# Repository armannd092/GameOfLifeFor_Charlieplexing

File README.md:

# GameOfLifeFor_Charlieplexing
It is a fun project for practicing electronic and algorithm.

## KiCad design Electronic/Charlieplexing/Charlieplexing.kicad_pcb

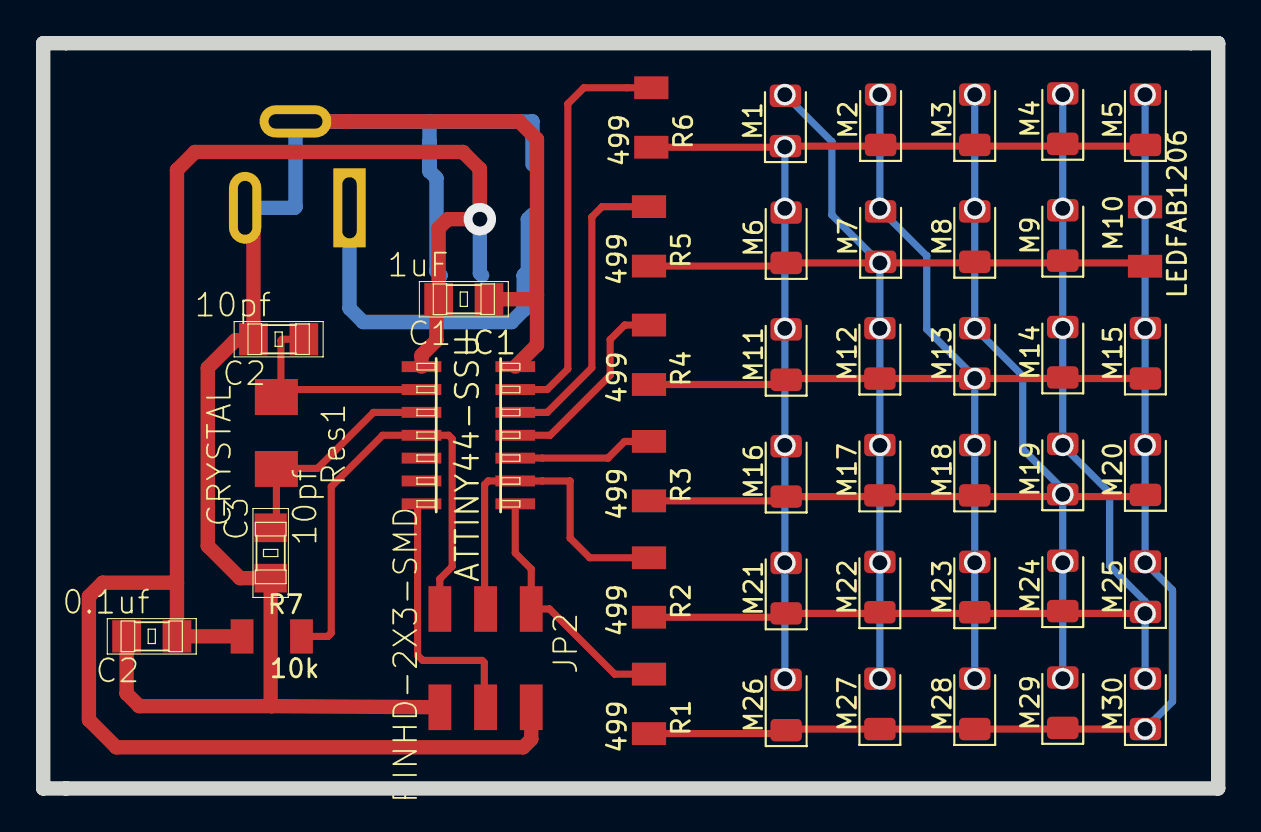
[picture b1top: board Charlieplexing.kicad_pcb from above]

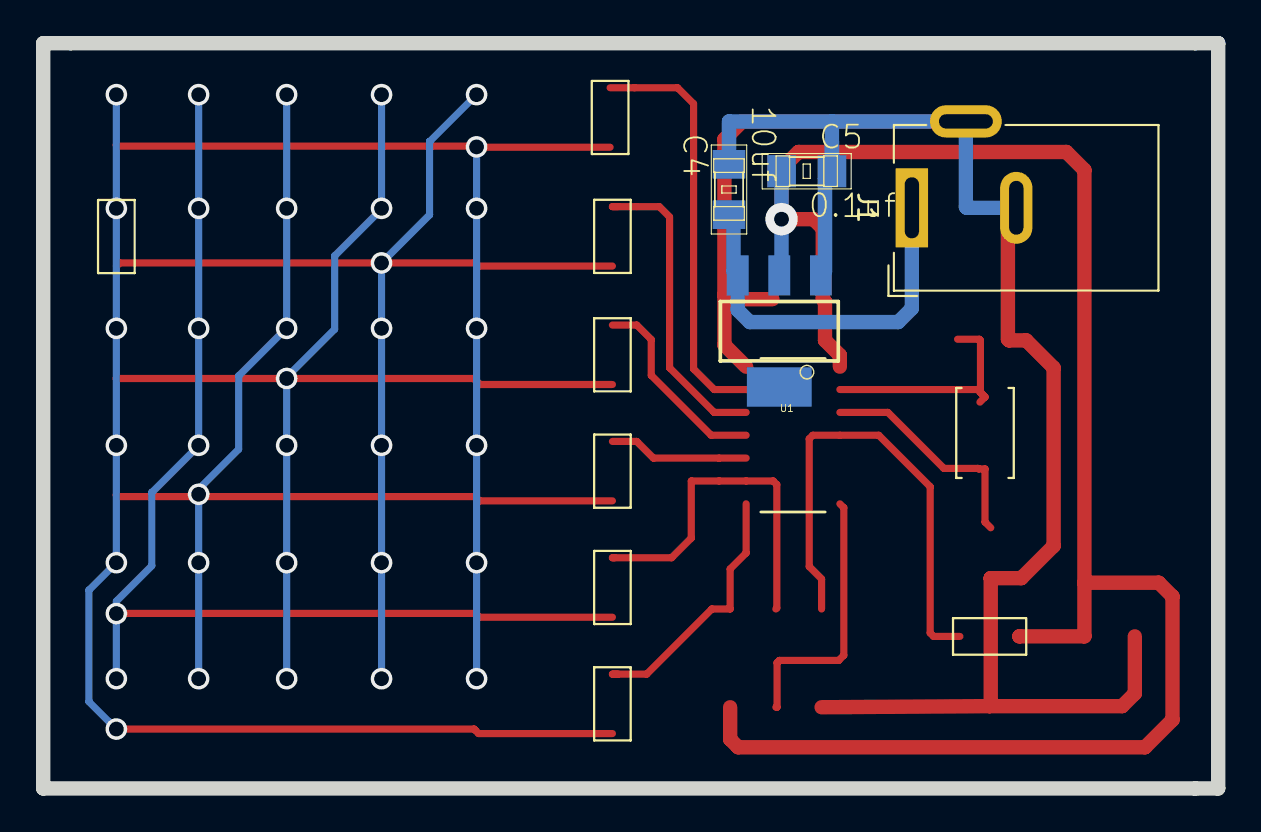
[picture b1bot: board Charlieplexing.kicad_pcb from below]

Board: 2 copper layers, 65.3 x 41.4 mm, 48 parts (4 on the bottom side), 19 nets.

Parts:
C1: 1uF; fab-C1206
C2, C5: 0.1uf; fab-C1206
C2#2, C3: 10pf; fab-C1206
C4: 10uf; fab-C1206
IC1: ATTINY44-SSU; fab-SOIC14
J1: Connector_Barrel_Jack_Switch; BarrelJack_Wuerth_6941xx301002
JP2: PINHD-2X3-SMD; fab-2X03SMD
M1, M2, M3, M4, M5, M6, M7, M8, M9, M11, M12, M13, M14, M15, M16, M17, M18, M19, M20, M21, M22, M23, M24, M25, M26, M27, M28, M29, M30: LEDFAB1206; LED_1206_3216Metric
M10: LEDFAB1206; fab-LED1206FAB
R1, R2, R3, R4, R5, R6: 499; fab-R1206FAB
R7: 10k; fab-R1206FAB
Res1: CRYSTAL; fab-2-SMD-5X3MM
U1: VOLTAGE-REGULATOR-SOT223; fab-SOT223

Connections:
5V: C1.2, C2.1, C5.1, IC1.1, JP2.2, R7.1, U1.2
GND: C1.1, C2.2, C2#2.2, C3.1, C4.2, C5.2, IC1.14, J1.2, J1.3, JP2.6, U1.1
MISO: IC1.8, JP2.1, R1.1
MOSI: IC1.7, JP2.4
unnamed: IC1.10, R3.1
unnamed: IC1.11, R4.1
unnamed: IC1.12, R5.1
unnamed: IC1.13, R6.1
Pin1: M1.1, M2.1, M3.1, M4.1, M5.1, M6.2, M11.2, M16.2, M21.2, M26.2, R6.2
Pin2: M1.2, M6.1, M7.1, M8.1, M9.1, M10.1, M12.2, M17.2, M22.2, M27.2, R5.2
Pin3: M2.2, M7.2, M11.1, M12.1, M13.1, M14.1, M15.1, M18.2, M23.2, M28.2, R4.2
Pin4: M3.2, M8.2, M13.2, M16.1, M17.1, M18.1, M19.1, M20.1, M24.2, M29.2, R3.2
Pin5: M4.2, M9.2, M14.2, M19.2, M21.1, M22.1, M23.1, M24.1, M25.1, M30.2, R2.2
Pin6: M5.2, M10.2, M15.2, M20.2, M25.2, M26.1, M27.1, M28.1, M29.1, M30.1, R1.2
REST: IC1.4, JP2.5, R7.2
SCK: IC1.9, JP2.3, R2.1
VIN: C4.1, J1.1, U1.3
XTAL1: C2#2.1, IC1.2, Res1.P$1
XTAL2: C3.2, IC1.3, Res1.P$2

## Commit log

2020-09-28 add electronic design files
2020-09-28 add ardunio init file
